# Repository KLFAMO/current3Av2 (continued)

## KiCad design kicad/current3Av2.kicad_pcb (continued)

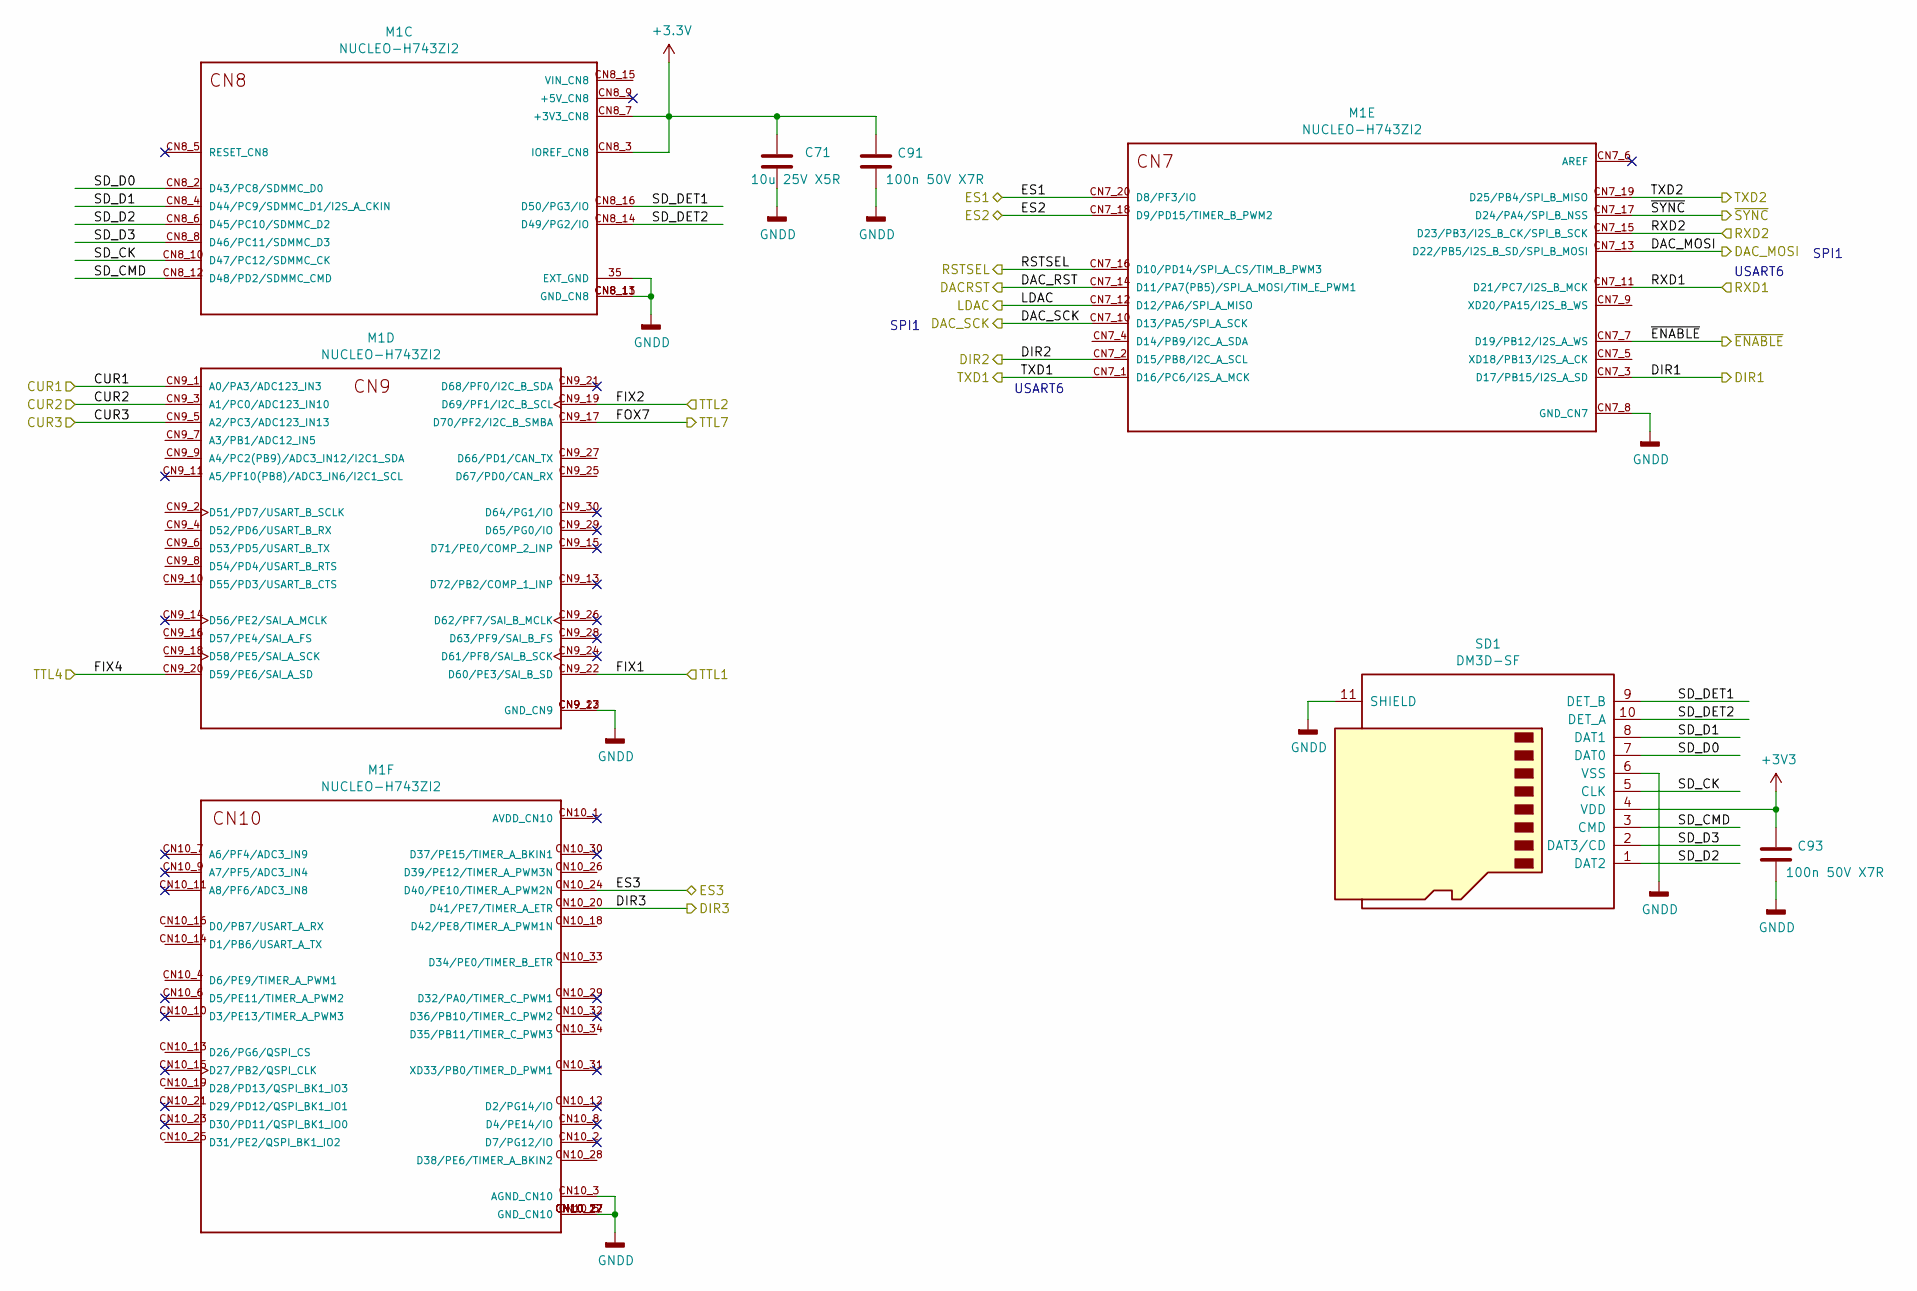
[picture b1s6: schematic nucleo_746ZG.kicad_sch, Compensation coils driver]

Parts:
C71: 10u 25V X5R; C_0603
C91, C93: 100n 50V X7R; C_0603
M1: NUCLEO-H743ZI2; MODULE_NUCLEO-F746ZG_mini_M
SD1: DM3D-SF; Hirose_DM3D-SF

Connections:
/CUR1: M1.CN9_1 (A0/PA3/ADC123_IN3); also elsewhere on the board
/CUR2: M1.CN9_3 (A1/PC0/ADC123_IN10); also elsewhere on the board
/CUR3: M1.CN9_5 (A2/PC3/ADC123_IN13); also elsewhere on the board
/DIR1: M1.CN7_3 (D17/PB15/I2S_A_SD); also elsewhere on the board
/DIR2: M1.CN7_2 (D15/PB8/I2C_A_SCL); also elsewhere on the board
/DIR3: M1.CN10_20 (D41/PE7/TIMER_A_ETR); also elsewhere on the board
/ES1: M1.CN7_20 (D8/PF3/IO); also elsewhere on the board
/ES2: M1.CN7_18 (D9/PD15/TIMER_B_PWM2); also elsewhere on the board
/ES3: M1.CN10_24 (D40/PE10/TIMER_A_PWM2N); also elsewhere on the board
/controller+DAC/DAC_MOSI: M1.CN7_13 (D22/PB5/I2S_B_SD/SPI_B_MOSI); also elsewhere on the board
/controller+DAC/DAC_SCK: M1.CN7_10 (D13/PA5/SPI_A_SCK); also elsewhere on the board
/controller+DAC/FIX1: M1.CN9_22 (D60/PE3/SAI_B_SD); also elsewhere on the board
/controller+DAC/FIX2: M1.CN9_19 (D69/PF1/I2C_B_SCL); also elsewhere on the board
/controller+DAC/FIX4: M1.CN9_20 (D59/PE6/SAI_A_SD); also elsewhere on the board
/controller+DAC/FOX7: M1.CN9_17 (D70/PF2/I2C_B_SMBA); also elsewhere on the board
/controller+DAC/LDAC: M1.CN7_12 (D12/PA6/SPI_A_MISO); also elsewhere on the board
/controller+DAC/RSTSEL: M1.CN7_16 (D10/PD14/SPI_A_CS/TIM_B_PWM3); also elsewhere on the board
/controller+DAC/RXD1: M1.CN7_11 (D21/PC7/I2S_B_MCK); also elsewhere on the board
/controller+DAC/RXD2: M1.CN7_15 (D23/PB3/I2S_B_CK/SPI_B_SCK); also elsewhere on the board
/controller+DAC/TXD1: M1.CN7_1 (D16/PC6/I2S_A_MCK); also elsewhere on the board
/controller+DAC/TXD2: M1.CN7_19 (D25/PB4/SPI_B_MISO); also elsewhere on the board
/controller+DAC/nucleo_746ZG/SD_CK: M1.CN8_10 (D47/PC12/SDMMC_CK), SD1.5 (CLK)
/controller+DAC/nucleo_746ZG/SD_CMD: M1.CN8_12 (D48/PD2/SDMMC_CMD), SD1.3 (CMD)
/controller+DAC/nucleo_746ZG/SD_D0: M1.CN8_2 (D43/PC8/SDMMC_D0), SD1.7 (DAT0)
/controller+DAC/nucleo_746ZG/SD_D1: M1.CN8_4 (D44/PC9/SDMMC_D1/I2S_A_CKIN), SD1.8 (DAT1)
/controller+DAC/nucleo_746ZG/SD_D2: M1.CN8_6 (D45/PC10/SDMMC_D2), SD1.1 (DAT2)
/controller+DAC/nucleo_746ZG/SD_D3: M1.CN8_8 (D46/PC11/SDMMC_D3), SD1.2 (DAT3/CD)
/controller+DAC/nucleo_746ZG/SD_DET1: M1.CN8_16 (D50/PG3/IO), SD1.9 (DET_B)
/controller+DAC/nucleo_746ZG/SD_DET2: M1.CN8_14 (D49/PG2/IO), SD1.10 (DET_A)
/controller+DAC/~ENABLE: M1.CN7_7 (D19/PB12/I2S_A_WS); also elsewhere on the board
/controller+DAC/~SYNC: M1.CN7_17 (D24/PA4/SPI_B_NSS); also elsewhere on the board
GND: C71.2, C91.2, C93.2, M1.35 (EXT_GND), M1.CN7_8 (GND_CN7), M1.CN8_11 (GND_CN8), M1.CN8_13 (GND_CN8), M1.CN9_12 (GND_CN9), M1.CN9_23 (GND_CN9), M1.CN10_3 (AGND_CN10), M1.CN10_5 (GND_CN10), M1.CN10_17 (GND_CN10), M1.CN10_22 (GND_CN10), M1.CN10_27 (GND_CN10), SD1.6 (VSS), SD1.11 (SHIELD); also elsewhere on the board

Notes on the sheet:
SPI1
USART6

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
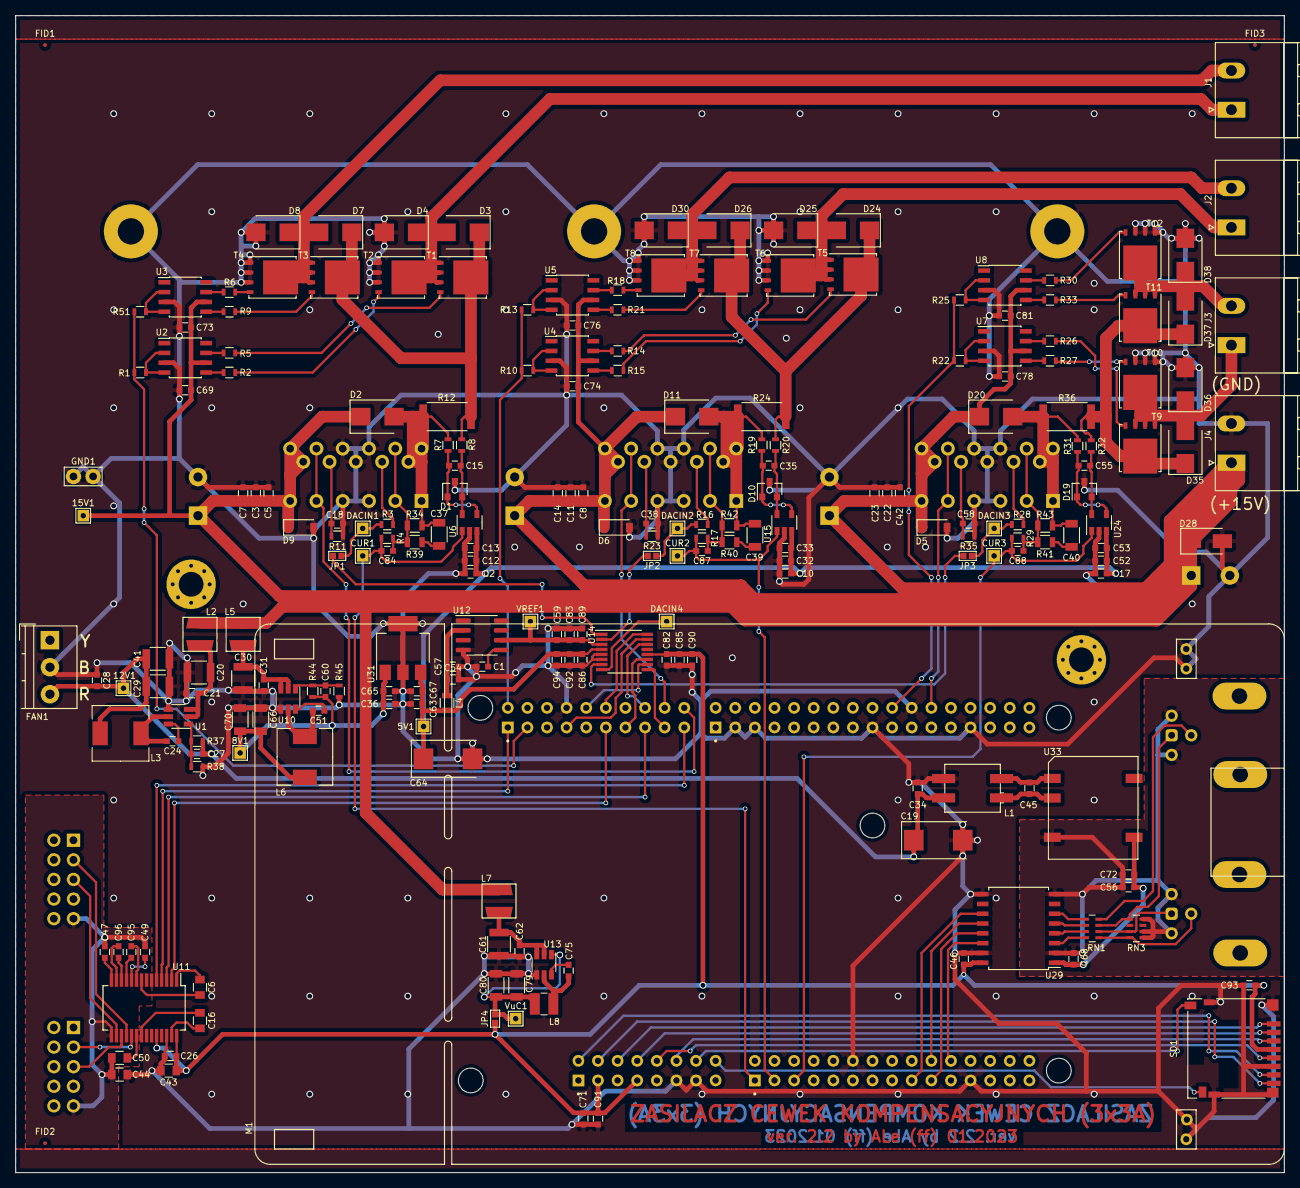
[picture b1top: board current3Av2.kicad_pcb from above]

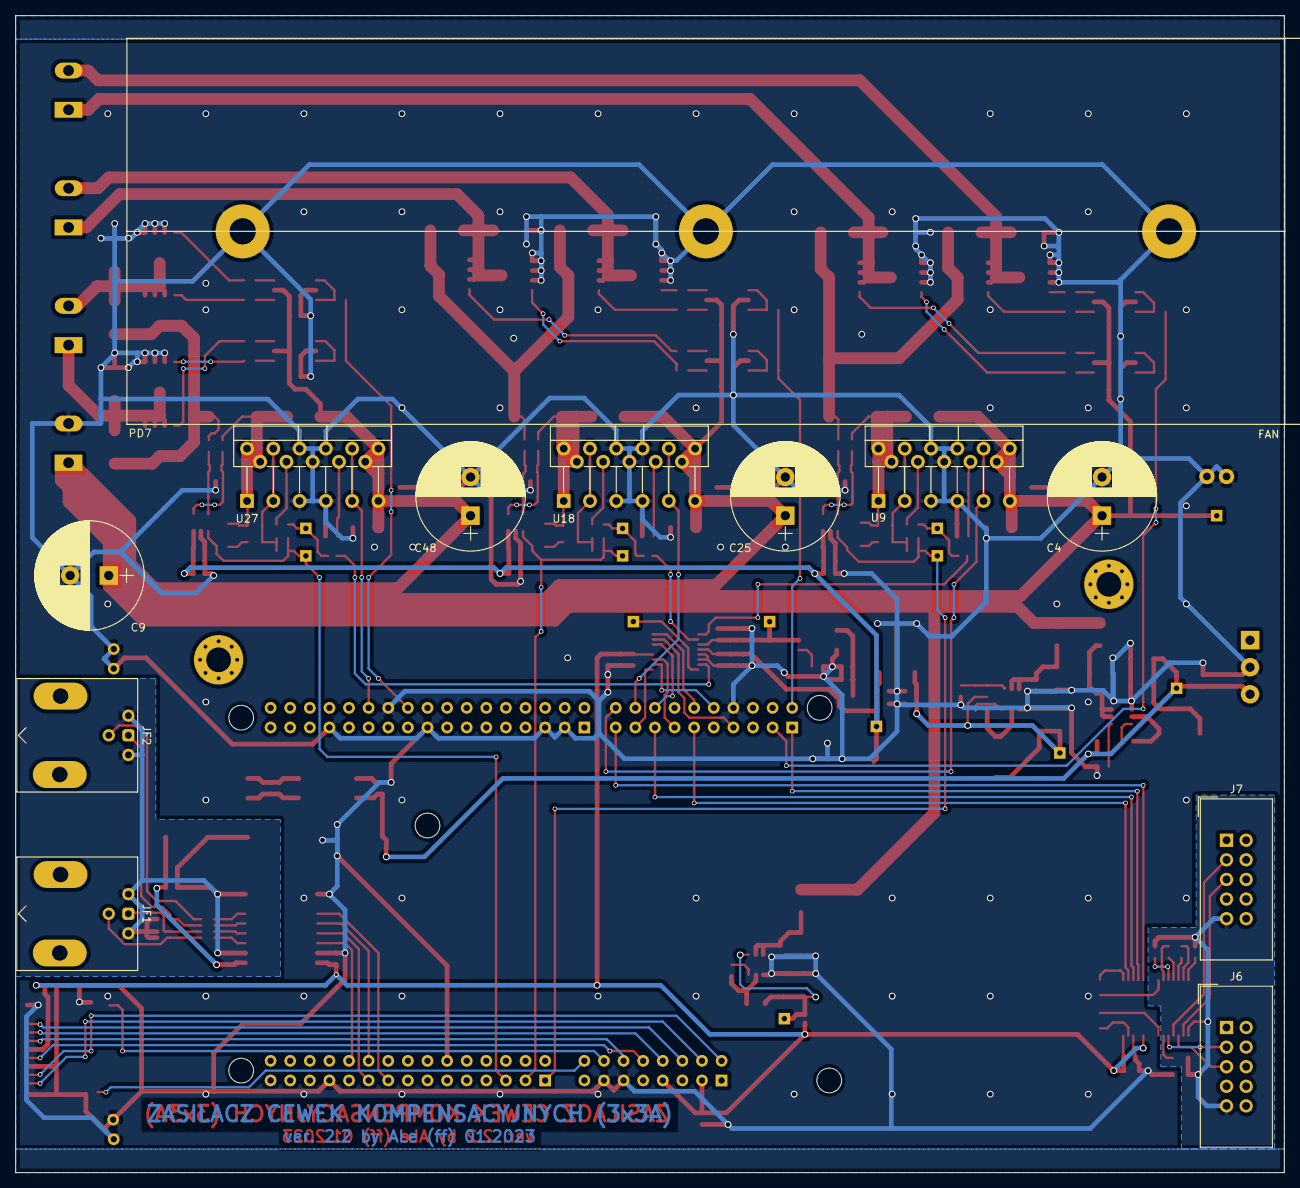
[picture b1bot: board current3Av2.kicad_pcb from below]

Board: 2 copper layers, 164.3 x 149.9 mm, 241 parts (12 on the bottom side), 147 nets.

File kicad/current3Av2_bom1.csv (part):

"Source:","D:\Projekty\FAMO\current3Av2\current3Av2.sch"
"Date:","03.01.2023 12:33:08"
"Tool:","Eeschema (5.1.12)-1"
"Generator:","C:\Program Files\KiCad\bin\scripting\plugins/bom_csv_grouped_by_value.py"
"Component Count:","241"

"Individual Components:"

"Item","Qty","Reference(s)","Value","LibPart","Footprint","Datasheet","Comm","Vendor"
"","","5V1","TestPoint","Connector:TestPoint","Connectors_TestPoints:Test_Point_THTPad_1.5x1.5mm_Drill0.7mm","~","",""
"","","8V1","TestPoint","Connector:TestPoint","Connectors_TestPoints:Test_Point_THTPad_1.5x1.5mm_Drill0.7mm","~","",""
"","","12V1","TestPoint","Connector:TestPoint","Connectors_TestPoints:Test_Point_THTPad_1.5x1.5mm_Drill0.7mm","~","",""
"","","15V1","TestPoint","Connector:TestPoint","Connectors_TestPoints:Test_Point_THTPad_1.5x1.5mm_Drill0.7mm","~","",""
"","","C1","1n C0G 50V","Device:C","Capacitors_SMD:C_0603","~","",""
"","","C2","10u 25V X5R","Device:C","Capacitors_SMD:C_0603","~","GRM188R61E106KA73D",""
"","","C3","10u 25V X5R","Device:C","Capacitors_SMD:C_0603","~","GRM188R61E106KA73D",""
"","","C4","2200u 16V 105°C ","Device:CP","Capacitors_THT:CP_Radial_D14.0mm_P5.00mm","~",">5000h Ø13x25mm P=5mm",""
"","","C5","100n 50V X7R","Device:C","Capacitors_SMD:C_0603","~","",""
"","","C6","470n 100V X7R","Device:C","Capacitors_SMD:C_0805","~","",""
"","","C7","10u 25V X5R","Device:C","Capacitors_SMD:C_0603","~","GRM188R61E106KA73D",""
"","","C8","100n 50V X7R","Device:C","Capacitors_SMD:C_0603","~","",""
"","","C9","2200u 16V 105°C ","Device:CP","Capacitors_THT:CP_Radial_D14.0mm_P5.00mm","~",">5000h Ø13x25mm P=5mm",""
"","","C10","10u 25V X5R","Device:C","Capacitors_SMD:C_0603","~","GRM188R61E106KA73D",""
"","","C11","10u 25V X5R","Device:C","Capacitors_SMD:C_0603","~","GRM188R61E106KA73D",""
"","","C12","100n 50V X7R","Device:C","Capacitors_SMD:C_0603","~","",""
"","","C13","100p C0G 50V","Device:C","Capacitors_SMD:C_0603","~","",""
"","","C14","10u 25V X5R","Device:C","Capacitors_SMD:C_0603","~","GRM188R61E106KA73D",""
"","","C15","1n C0G 50V","Device:C","Capacitors_SMD:C_0603","~","",""
"","","C16","470n 100V X7R","Device:C","Capacitors_SMD:C_0805","~","",""
"","","C17","10u 25V X5R","Device:C","Capacitors_SMD:C_0603","~","GRM188R61E106KA73D",""
"","","C18","100n 50V X7R","Device:C","Capacitors_SMD:C_0603","~","",""
"","","C19","100u 16V","Device:CP","Capacitors_Tantalum_SMD:CP_Tantalum_Case-D_EIA-7343-31_Reflow","~","tantal, case D",""
"","","C20","GRM32ER71H106KA12L","Device:C","Capacitors_SMD:C_1210","~","10u 50V X7R Murata",""
"","","C21","100n 50V X7R","Device:C","Capacitors_SMD:C_0603","~","",""
"","","C22","10u 25V X5R","Device:C","Capacitors_SMD:C_0603","~","GRM188R61E106KA73D",""
"","","C23","10u 25V X5R","Device:C","Capacitors_SMD:C_0603","~","GRM188R61E106KA73D",""
"","","C24","100n 50V X7R","Device:C","Capacitors_SMD:C_0603","~","",""
"","","C25","2200u 16V 105°C ","Device:CP","Capacitors_THT:CP_Radial_D14.0mm_P5.00mm","~",">5000h Ø13x25mm P=5mm",""
"","","C26","100n 50V X7R","Device:C","Capacitors_SMD:C_0603","~","",""
"","","C27","56p 50V C0G","Device:C","Capacitors_SMD:C_0603","~","",""
"","","C28","10u 25V X5R","Device:C","Capacitors_SMD:C_0603","~","GRM188R61E106KA73D",""
"","","C29","GRM32ER71E226KE15K","Device:C","Capacitors_SMD:C_1210","~","22u 25V X7R Murata",""
"","","C30","GRM32ER71H106KA12L","Device:C","Capacitors_SMD:C_1210","~","10u 50V X7R Murata",""
"","","C31","100n 50V X7R","Device:C","Capacitors_SMD:C_0603","~","",""
"","","C32","100n 50V X7R","Device:C","Capacitors_SMD:C_0603","~","",""
"","","C33","100p C0G 50V","Device:C","Capacitors_SMD:C_0603","~","",""
"","","C34","10u 25V X5R","Device:C","Capacitors_SMD:C_0603","~","GRM188R61E106KA73D",""
"","","C35","1n C0G 50V","Device:C","Capacitors_SMD:C_0603","~","",""
"","","C36","10u 25V X5R","Device:C","Capacitors_SMD:C_0603","~","GRM188R61E106KA73D",""
"","","C37","100n 50V C0G","Device:C","Capacitors_SMD:C_1206","~","",""
"","","C38","100n 50V X7R","Device:C","Capacitors_SMD:C_0603","~","",""
"","","C39","100n 50V C0G","Device:C","Capacitors_SMD:C_1206","~","",""
"","","C40","100n 50V C0G","Device:C","Capacitors_SMD:C_1206","~","",""
"","","C41","GRM32ER71E226KE15K","Device:C","Capacitors_SMD:C_1210","~","22u 25V X7R Murata",""
"","","C42","100n 50V X7R","Device:C","Capacitors_SMD:C_0603","~","",""
"","","C43","2,2u 25V X7R","Device:C","Capacitors_SMD:C_0805","~","",""
"","","C44","10n 100V X7R","Device:C","Capacitors_SMD:C_0805","~","",""
"","","C45","10u 25V X5R","Device:C","Capacitors_SMD:C_0603","~","GRM188R61E106KA73D",""
"","","C46","100n 50V X7R","Device:C","Capacitors_SMD:C_0603","~","",""
"","","C47","470n 25V X7R","Device:C","Capacitors_SMD:C_0603","~","",""
"","","C48","2200u 16V 105°C ","Device:CP","Capacitors_THT:CP_Radial_D14.0mm_P5.00mm","~",">5000h Ø13x25mm P=5mm",""
"","","C49","470n 25V X7R","Device:C","Capacitors_SMD:C_0603","~","",""
"","","C50","2,2u 25V X7R","Device:C","Capacitors_SMD:C_0805","~","",""
"","","C51","100n 50V X7R","Device:C","Capacitors_SMD:C_0603","~","",""
"","","C52","100n 50V X7R","Device:C","Capacitors_SMD:C_0603","~","",""
"","","C53","100p C0G 50V","Device:C","Capacitors_SMD:C_0603","~","",""
"","","C54","10u 25V X5R","Device:C","Capacitors_SMD:C_0603","~","GRM188R61E106KA73D",""
"","","C55","1n C0G 50V","Device:C","Capacitors_SMD:C_0603","~","",""
"","","C56","10u 25V X5R","Device:C","Capacitors_SMD:C_0603","~","GRM188R61E106KA73D",""
"","","C57","1u 25V X7R","Device:C","Capacitors_SMD:C_0603","~","",""
"","","C58","100n 50V X7R","Device:C","Capacitors_SMD:C_0603","~","",""
"","","C59","1u 25V X7R","Device:C","Capacitors_SMD:C_0603","~","",""
"","","C60","82p 50V C0G","Device:C","Capacitors_SMD:C_0603","~","",""
"","","C61","GRM32ER71H106KA12L","Device:C","Capacitors_SMD:C_1210","~","10u 50V X7R Murata",""
"","","C62","100n 50V X7R","Device:C","Capacitors_SMD:C_0603","~","",""
"","","C63","10u 25V X5R","Device:C","Capacitors_SMD:C_0603","~","GRM188R61E106KA73D",""
"","","C64","100u 16V","Device:CP","Capacitors_Tantalum_SMD:CP_Tantalum_Case-D_EIA-7343-31_Reflow","~","tantal, case D",""
"","","C65","100n 50V X7R","Device:C","Capacitors_SMD:C_0603","~","",""
"","","C66","GRM31CR71A226KE15L","Device:C","Capacitors_SMD:C_1206","~","22u 10V X7R Murata",""
"","","C67","100n 50V X7R","Device:C","Capacitors_SMD:C_0603","~","",""
"","","C68","100n 50V X7R","Device:C","Capacitors_SMD:C_0603","~","",""
"","","C69","100n 50V X7R","Device:C","Capacitors_SMD:C_0603","~","",""
"","","C70","GRM31CR71A226KE15L","Device:C","Capacitors_SMD:C_1206","~","22u 10V X7R Murata",""
"","","C71","10u 25V X5R","Device:C","Capacitors_SMD:C_0603","~","GRM188R61E106KA73D",""
"","","C72","100n 50V X7R","Device:C","Capacitors_SMD:C_0603","~","",""
"","","C73","100p C0G 50V","Device:C","Capacitors_SMD:C_0603","~","",""
"","","C74","100n 50V X7R","Device:C","Capacitors_SMD:C_0603","~","",""
"","","C75","100n 50V X7R","Device:C","Capacitors_SMD:C_0603","~","",""
"","","C76","100p C0G 50V","Device:C","Capacitors_SMD:C_0603","~","",""
"","","C78","100n 50V X7R","Device:C","Capacitors_SMD:C_0603","~","",""
"","","C79","GRM31CR71A226KE15L","Device:C","Capacitors_SMD:C_1206","~","22u 10V X7R Murata",""
"","","C80","GRM31CR71A226KE15L","Device:C","Capacitors_SMD:C_1206","~","22u 10V X7R Murata",""
"","","C81","100p C0G 50V","Device:C","Capacitors_SMD:C_0603","~","",""
"","","C82","100p 50V C0G","Device:C","Capacitors_SMD:C_0603","~","",""
"","","C83","100n 50V X7R","Device:C","Capacitors_SMD:C_0603","~","",""
"","","C84","DNP","Device:C","Capacitors_SMD:C_0603","~","",""
"","","C85","100n 50V X7R","Device:C","Capacitors_SMD:C_0603","~","",""
"","","C86","100p 50V C0G","Device:C","Capacitors_SMD:C_0603","~","",""
"","","C87","DNP","Device:C","Capacitors_SMD:C_0603","~","",""
"","","C88","DNP","Device:C","Capacitors_SMD:C_0603","~","",""
"","","C89","100p 50V C0G","Device:C","Capacitors_SMD:C_0603","~","",""
"","","C90","10u 25V X5R","Device:C","Capacitors_SMD:C_0603","~","GRM188R61E106KA73D",""
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
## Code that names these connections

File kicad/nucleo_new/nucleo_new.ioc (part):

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Mcu.Name=STM32H743ZITx
Mcu.Package=LQFP144
Mcu.UserName=STM32H743ZITx
PA1.Mode=RMII
PA1.Signal=ETH_REF_CLK
PA11.Mode=Device_Only
PA11.Signal=USB_OTG_FS_DM
PA12.Mode=Device_Only
PA12.Signal=USB_OTG_FS_DP
PA2.Mode=RMII
PA2.Signal=ETH_MDIO
PA3.GPIOParameters=GPIO_Label
PA3.GPIO_Label=CUR3
PA3.Signal=ADCx_INP15
PA5.GPIOParameters=GPIO_Label
PA5.GPIO_Label=A20
PA5.Signal=COMP_DAC12_group
PA7.Mode=RMII
PA7.Signal=ETH_CRS_DV
PA8.Mode=Activate_SOF_FS
PA8.Signal=USB_OTG_FS_SOF
PA9.Mode=Activate_VBUS
PA9.Signal=USB_OTG_FS_VBUS
PB0.GPIOParameters=GPIO_Label
PB0.GPIO_Label=LD1 [Green Led]
PB0.Signal=GPIO_Output
PB13.Mode=RMII
PB13.Signal=ETH_TXD1
PB14.GPIOParameters=GPIO_Label
PB14.GPIO_Label=LD3 [Red Led]
PB14.Signal=GPIO_Output
PB8.GPIOParameters=GPIO_Label
PB8.GPIO_Label=DIR3
PB8.Signal=GPIO_Output
PB9.GPIOParameters=GPIO_Label
PB9.GPIO_Label=DIR2
PB9.Signal=GPIO_Output
PC0.GPIOParameters=GPIO_Label
PC0.GPIO_Label=CUR2
PC0.Signal=ADCx_INP10
PC1.Mode=RMII
PC1.Signal=ETH_MDC
PC10.GPIOParameters=GPIO_Label
PC10.GPIO_Label=SD_D2
PC10.Mode=SD_4_bits_Wide_bus
PC10.Signal=SDMMC1_D2
PC11.GPIOParameters=GPIO_Label
PC11.GPIO_Label=SD_D3
PC11.Mode=SD_4_bits_Wide_bus
PC11.Signal=SDMMC1_D3
PC12.GPIOParameters=GPIO_Label
PC12.GPIO_Label=SD_CK
PC12.Mode=SD_4_bits_Wide_bus
PC12.Signal=SDMMC1_CK
PC13.GPIOParameters=GPIO_Label
PC13.GPIO_Label=B1 [Blue PushButton]
PC13.Signal=GPIO_Input
PC14-OSC32_IN\ (OSC32_IN).Mode=LSE-External-Oscillator
PC14-OSC32_IN\ (OSC32_IN).Signal=RCC_OSC32_IN
PC15-OSC32_OUT\ (OSC32_OUT).Mode=LSE-External-Oscillator
PC15-OSC32_OUT\ (OSC32_OUT).Signal=RCC_OSC32_OUT
PC2_C.GPIOParameters=GPIO_Label
PC2_C.GPIO_Label=CUR1
PC2_C.Mode=IN0-Single-Ended
PC2_C.Signal=ADC3_INP0
PC4.Mode=RMII
PC4.Signal=ETH_RXD0
PC5.Mode=RMII
PC5.Signal=ETH_RXD1
PC6.GPIOParameters=GPIO_Label
PC6.GPIO_Label=TXD1
PC6.Mode=Asynchronous
PC6.Signal=USART6_TX
PC7.GPIOParameters=GPIO_Label
PC7.GPIO_Label=RXD1
PC7.Mode=Asynchronous
PC7.Signal=USART6_RX
PC8.GPIOParameters=GPIO_Label
PC8.GPIO_Label=SD_D0
PC8.Mode=SD_4_bits_Wide_bus
PC8.Signal=SDMMC1_D0
PC9.GPIOParameters=GPIO_Label
PC9.GPIO_Label=SD_D1
PC9.Mode=SD_4_bits_Wide_bus
PC9.Signal=SDMMC1_D1
PD0.GPIOParameters=GPIO_Label
PD0.GPIO_Label=FIX2
PD0.Signal=GPIO_Input
PD1.GPIOParameters=GPIO_Label
PD1.GPIO_Label=FIX4
PD1.Signal=GPIO_Input
PD10.GPIOParameters=GPIO_Label
PD10.GPIO_Label=USB_OTG_FS_PWR_EN
PD10.Signal=GPIO_Output
PD2.GPIOParameters=GPIO_Label
PD2.GPIO_Label=SD_CMD
PD2.Mode=SD_4_bits_Wide_bus
PD2.Signal=SDMMC1_CMD
PD3.GPIOParameters=GPIO_Label
PD3.GPIO_Label=FANERR
PD3.Signal=GPIO_Input
PD4.GPIOParameters=GPIO_Label
PD4.GPIO_Label=FANON
PD4.Signal=GPIO_Output
PD5.GPIOParameters=GPIO_Label
PD5.GPIO_Label=TXD2
PD5.Mode=Asynchronous
PD5.Signal=USART2_TX
PD6.GPIOParameters=GPIO_Label
PD6.GPIO_Label=RXD2
PD6.Mode=Asynchronous
PD6.Signal=USART2_RX
PD7.GPIOParameters=GPIO_Label
PD7.GPIO_Label=DIR1
PD7.Signal=GPIO_Output
PD8.GPIOParameters=GPIO_Label
PD8.GPIO_Label=STLINK_RX
PD8.Mode=Asynchronous
PD8.Signal=USART3_TX
PD9.GPIOParameters=GPIO_Label
PD9.GPIO_Label=STLINK_TX
PD9.Mode=Asynchronous
PD9.Signal=USART3_RX
PE1.GPIOParameters=GPIO_Label
PE1.GPIO_Label=LD2 [Yellow Led]
PE1.Signal=GPIO_Output
PE12.GPIOParameters=GPIO_Label
PE12.GPIO_Label=DAC_SCK
PE12.Mode=TX_Only_Simplex_Unidirect_Master
PE12.Signal=SPI4_SCK
PE2.GPIOParameters=GPIO_Label
PE2.GPIO_Label=FIX3
PE2.Signal=GPIO_Input
PE3.GPIOParameters=GPIO_Label
PE3.GPIO_Label=FIX5
PE3.Signal=GPIO_Input
PE4.GPIOParameters=GPIO_Label
PE4.GPIO_Label=DAC_CS1
PE4.Signal=GPIO_Output
PE5.GPIOParameters=GPIO_Label
PE5.GPIO_Label=DAC_CS2
PE5.Signal=GPIO_Output
PE6.GPIOParameters=GPIO_Label
PE6.GPIO_Label=DAC_MOSI
PE6.Mode=TX_Only_Simplex_Unidirect_Master
PE6.Signal=SPI4_MOSI
PE8.GPIOParameters=GPIO_Label
PE8.GPIO_Label=FOX7
PE8.Signal=GPIO_Output
PE9.GPIOParameters=GPIO_Label
PE9.GPIO_Label=FOX8
PE9.Signal=GPIO_Output
PF1.GPIOParameters=GPIO_Label
PF1.GPIO_Label=DAC_CS3
PF1.Signal=GPIO_Output
PF3.GPIOParameters=GPIO_Label
PF3.GPIO_Label=TH1
PF3.Mode=IN5-Single-Ended
PF3.Signal=ADC3_INP5
PF5.GPIOParameters=GPIO_Label
PF5.GPIO_Label=TH2
PF5.Mode=IN4-Single-Ended
PF5.Signal=ADC3_INP4
PG11.Mode=RMII
PG11.Signal=ETH_TX_EN
PG13.Mode=RMII
PG13.Signal=ETH_TXD0
PG2.GPIOParameters=GPIO_Label
PG2.GPIO_Label=SD_DET2
PG2.Signal=GPIO_Input
PG3.GPIOParameters=GPIO_Label
PG3.GPIO_Label=SD_DET1
PG3.Signal=GPIO_Input
PG7.GPIOParameters=GPIO_Label
PG7.GPIO_Label=USB_OTG_FS_OVCR
PG7.Signal=GPXTI7
PH0-OSC_IN\ (PH0).Mode=HSE-External-Clock-Source
PH0-OSC_IN\ (PH0).Signal=RCC_OSC_IN
PH1-OSC_OUT\ (PH1).Signal=RCC_OSC_OUT
RCC.HSE_VALUE=8000000
RCC.SYSCLKFreq_VALUE=64000000
board=NUCLEO-H743ZI2
boardIOC=true

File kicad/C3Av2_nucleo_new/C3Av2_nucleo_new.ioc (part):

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Mcu.Name=STM32H743ZITx
Mcu.Package=LQFP144
Mcu.UserName=STM32H743ZITx
PA1.Mode=RMII
PA1.Signal=ETH_REF_CLK
PA11.Mode=Device_Only
PA11.Signal=USB_OTG_FS_DM
PA12.Mode=Device_Only
PA12.Signal=USB_OTG_FS_DP
PA13\ (JTMS/SWDIO).Mode=JTAG_4_pins
PA13\ (JTMS/SWDIO).Signal=DEBUG_JTMS-SWDIO
PA14\ (JTCK/SWCLK).Mode=JTAG_4_pins
PA14\ (JTCK/SWCLK).Signal=DEBUG_JTCK-SWCLK
PA15\ (JTDI).Mode=JTAG_4_pins
PA15\ (JTDI).Signal=DEBUG_JTDI
PA2.Mode=RMII
PA2.Signal=ETH_MDIO
PA3.GPIOParameters=GPIO_Label
PA3.GPIO_Label=CUR1(ADC1)
PA3.Signal=ADCx_INP15
PA4.GPIOParameters=GPIO_Label
PA4.GPIO_Label=DAC1_CS(out)
PA4.Signal=GPIO_Output
PA5.GPIOParameters=GPIO_Label
PA5.GPIO_Label=DAC_SCK(SPI1)
PA5.Mode=TX_Only_Simplex_Unidirect_Master
PA5.Signal=SPI1_SCK
PA6.GPIOParameters=GPIO_Label
PA6.GPIO_Label=DAC3_CS(out)
PA6.Signal=GPIO_Output
PA7.Mode=RMII
PA7.Signal=ETH_CRS_DV
PA8.Mode=Activate_SOF_FS
PA8.Signal=USB_OTG_FS_SOF
PA9.Mode=Activate_VBUS
PA9.Signal=USB_OTG_FS_VBUS
PB0.GPIOParameters=GPIO_Label
PB0.GPIO_Label=LD1 [Green Led]
PB0.Signal=GPIO_Output
PB11.GPIOParameters=GPIO_Label
PB11.GPIO_Label=FIX2(EXTI11)
PB11.Signal=GPXTI11
PB12.GPIOParameters=GPIO_Label
PB12.GPIO_Label=DAC2_CS(out)
PB12.Signal=GPIO_Output
PB13.Mode=RMII
PB13.Signal=ETH_TXD1
PB14.GPIOParameters=GPIO_Label
PB14.GPIO_Label=LD3 [Red Led]
PB14.Signal=GPIO_Output
PB15.GPIOParameters=GPIO_Label
PB15.GPIO_Label=DIR1(out)
PB15.Signal=GPIO_Output
PB3\ (JTDO/TRACESWO).Mode=JTAG_4_pins
PB3\ (JTDO/TRACESWO).Signal=DEBUG_JTDO-SWO
PB5.GPIOParameters=GPIO_Label
PB5.GPIO_Label=DAC_MOSI(SPI1)
PB5.Mode=TX_Only_Simplex_Unidirect_Master
PB5.Signal=SPI1_MOSI
PB6.GPIOParameters=GPIO_Label
PB6.GPIO_Label=TDX2
PB6.Mode=Asynchronous
PB6.Signal=USART1_TX
PB7.GPIOParameters=GPIO_Label
PB7.GPIO_Label=RXD2
PB7.Mode=Asynchronous
PB7.Signal=USART1_RX
PB8.GPIOParameters=GPIO_Label
PB8.GPIO_Label=DIR2(out)
PB8.Signal=GPIO_Output
PB9.GPIOParameters=GPIO_Label
PB9.GPIO_Label=DIR3(out)
PB9.Signal=GPIO_Output
PC0.GPIOParameters=GPIO_Label
PC0.GPIO_Label=CUR2(ADC2)
PC0.Signal=ADCx_INP10
PC1.Mode=RMII
PC1.Signal=ETH_MDC
PC10.Mode=SD_4_bits_Wide_bus
PC10.Signal=SDMMC1_D2
PC11.Mode=SD_4_bits_Wide_bus
PC11.Signal=SDMMC1_D3
PC12.Mode=SD_4_bits_Wide_bus
PC12.Signal=SDMMC1_CK
PC13.GPIOParameters=GPIO_Label
PC13.GPIO_Label=B1 [Blue PushButton]
PC13.Signal=GPIO_Input
PC14-OSC32_IN\ (OSC32_IN).Mode=LSE-External-Oscillator
PC14-OSC32_IN\ (OSC32_IN).Signal=RCC_OSC32_IN
PC15-OSC32_OUT\ (OSC32_OUT).Mode=LSE-External-Oscillator
PC15-OSC32_OUT\ (OSC32_OUT).Signal=RCC_OSC32_OUT
PC3_C.GPIOParameters=GPIO_Label
PC3_C.GPIO_Label=CUR3(ADC3)
PC3_C.Mode=IN1-Single-Ended
PC3_C.Signal=ADC3_INP1
PC4.Mode=RMII
PC4.Signal=ETH_RXD0
PC5.Mode=RMII
PC5.Signal=ETH_RXD1
PC6.GPIOParameters=GPIO_Label
PC6.GPIO_Label=TXD1
PC6.Mode=Asynchronous
PC6.Signal=USART6_TX
PC7.GPIOParameters=GPIO_Label
PC7.GPIO_Label=RXD1
PC7.Mode=Asynchronous
PC7.Signal=USART6_RX
PC8.Mode=SD_4_bits_Wide_bus
PC8.Signal=SDMMC1_D0
PC9.Mode=SD_4_bits_Wide_bus
PC9.Signal=SDMMC1_D1
PD10.GPIOParameters=GPIO_Label
PD10.GPIO_Label=USB_OTG_FS_PWR_EN
PD10.Signal=GPIO_Output
PD2.Mode=SD_4_bits_Wide_bus
PD2.Signal=SDMMC1_CMD
PD8.GPIOParameters=GPIO_Label
PD8.GPIO_Label=STLINK_RX
PD8.Mode=Asynchronous
PD8.Signal=USART3_TX
PD9.GPIOParameters=GPIO_Label
PD9.GPIO_Label=STLINK_TX
PD9.Mode=Asynchronous
PD9.Signal=USART3_RX
PE0.GPIOParameters=GPIO_Label
PE0.GPIO_Label=FIX1(EXTI0)
PE0.Signal=GPXTI0
PE1.GPIOParameters=GPIO_Label
PE1.GPIO_Label=LD2 [Yellow Led]
PE1.Signal=GPIO_Output
PE10.GPIOParameters=GPIO_Label
PE10.GPIO_Label=FIX4(PE10)
PE10.Signal=GPXTI10
PE12.GPIOParameters=GPIO_Label
PE12.GPIO_Label=FIX5(EXTI12)
PE12.Signal=GPXTI12
PE6.GPIOParameters=GPIO_Label
PE6.GPIO_Label=FIX3(EXTI6)
PE6.Signal=GPXTI6
PE7.GPIOParameters=GPIO_Label
PE7.GPIO_Label=FIX6(EXTI7)
PE7.Signal=GPXTI7
PE8.GPIOParameters=GPIO_Label
PE8.GPIO_Label=FOX7(out)
PE8.Signal=GPIO_Output
PE9.GPIOParameters=GPIO_Label
PE9.GPIO_Label=FOX8(out)
PE9.Signal=GPIO_Output
PG11.Mode=RMII
PG11.Signal=ETH_TX_EN
PG13.Mode=RMII
PG13.Signal=ETH_TXD0
PG2.GPIOParameters=GPIO_Label
PG2.GPIO_Label=SD_DET2(EXTI2)
PG2.Signal=GPXTI2
PG3.GPIOParameters=GPIO_Label
PG3.GPIO_Label=SD_DET1(EXTI3)
PG3.Signal=GPXTI3
PH0-OSC_IN\ (PH0).Mode=HSE-External-Clock-Source
PH0-OSC_IN\ (PH0).Signal=RCC_OSC_IN
PH1-OSC_OUT\ (PH1).Signal=RCC_OSC_OUT
RCC.HSE_VALUE=8000000
RCC.SYSCLKFreq_VALUE=64000000
board=NUCLEO-H743ZI2
boardIOC=true

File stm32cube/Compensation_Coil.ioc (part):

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Mcu.Name=STM32H743ZITx
Mcu.Package=LQFP144
Mcu.UserName=STM32H743ZITx
PA1.GPIOParameters=GPIO_Speed
PA1.GPIO_Speed=GPIO_SPEED_FREQ_HIGH
PA1.Mode=RMII
PA1.Signal=ETH_REF_CLK
PA2.GPIOParameters=GPIO_Speed
PA2.GPIO_Speed=GPIO_SPEED_FREQ_HIGH
PA2.Mode=RMII
PA2.Signal=ETH_MDIO
PA4.GPIOParameters=GPIO_Label
PA4.GPIO_Label=SYNC
PA4.Mode=NSS_Signal_Hard_Output
PA4.Signal=SPI1_NSS
PA5.GPIOParameters=GPIO_Label
PA5.GPIO_Label=DAC_SCK
PA5.Mode=TX_Only_Simplex_Unidirect_Master
PA5.Signal=SPI1_SCK
PA6.GPIOParameters=GPIO_Label
PA6.GPIO_Label=LDAC
PA6.Signal=GPIO_Output
PA7.GPIOParameters=GPIO_Speed
PA7.GPIO_Speed=GPIO_SPEED_FREQ_HIGH
PA7.Mode=RMII
PA7.Signal=ETH_CRS_DV
PB0.GPIOParameters=GPIO_Speed,GPIO_Label
PB0.GPIO_Label=LD1 [Green Led]
PB0.GPIO_Speed=GPIO_SPEED_FREQ_VERY_HIGH
PB0.Signal=GPIO_Output
PB12.GPIOParameters=GPIO_Label
PB12.GPIO_Label=ENABLE
PB12.Signal=GPIO_Output
PB13.GPIOParameters=GPIO_Speed
PB13.GPIO_Speed=GPIO_SPEED_FREQ_HIGH
PB13.Mode=RMII
PB13.Signal=ETH_TXD1
PB14.GPIOParameters=GPIO_Speed,GPIO_Label
PB14.GPIO_Label=LD3 [Red Led]
PB14.GPIO_Speed=GPIO_SPEED_FREQ_VERY_HIGH
PB14.Signal=GPIO_Output
PB15.GPIOParameters=GPIO_Label
PB15.GPIO_Label=DIR1
PB15.Signal=GPIO_Output
PB5.GPIOParameters=GPIO_Label
PB5.GPIO_Label=DAC_MOSI
PB5.Mode=TX_Only_Simplex_Unidirect_Master
PB5.Signal=SPI1_MOSI
PB8.GPIOParameters=GPIO_Label
PB8.GPIO_Label=DIR2
PB8.Signal=GPIO_Output
PC1.GPIOParameters=GPIO_Speed
PC1.GPIO_Speed=GPIO_SPEED_FREQ_HIGH
PC1.Mode=RMII
PC1.Signal=ETH_MDC
PC13.Signal=GPXTI13
PC4.GPIOParameters=GPIO_Speed
PC4.GPIO_Speed=GPIO_SPEED_FREQ_HIGH
PC4.Mode=RMII
PC4.Signal=ETH_RXD0
PC5.GPIOParameters=GPIO_Speed
PC5.GPIO_Speed=GPIO_SPEED_FREQ_HIGH
PC5.Mode=RMII
PC5.Signal=ETH_RXD1
PD14.GPIOParameters=GPIO_Label
PD14.GPIO_Label=RSTSEL
PD14.Signal=GPIO_Output
PD8.GPIOParameters=GPIO_Speed,GPIO_Label
PD8.GPIO_Label=STLINK_RX
PD8.GPIO_Speed=GPIO_SPEED_FREQ_HIGH
PD8.Mode=Asynchronous
PD8.Signal=USART3_TX
PD9.GPIOParameters=GPIO_Speed,GPIO_Label
PD9.GPIO_Label=STLINK_TX
PD9.GPIO_Speed=GPIO_SPEED_FREQ_HIGH
PD9.Mode=Asynchronous
PD9.Signal=USART3_RX
PE1.GPIOParameters=GPIO_Speed,GPIO_Label
PE1.GPIO_Label=LD2 [Yellow Led]
PE1.GPIO_Speed=GPIO_SPEED_FREQ_VERY_HIGH
PE1.Signal=GPIO_Output
PE3.GPIOParameters=GPIO_PuPd,GPIO_Label
PE3.GPIO_Label=TTL1
PE3.GPIO_PuPd=GPIO_PULLDOWN
PE3.Signal=GPIO_Input
PE6.GPIOParameters=GPIO_Label,GPIO_ModeDefaultEXTI
PE6.GPIO_Label=TTL3
PE6.GPIO_ModeDefaultEXTI=GPIO_MODE_IT_RISING
PE6.Signal=GPXTI6
PE7.GPIOParameters=GPIO_Label
PE7.GPIO_Label=DIR3
PE7.Signal=GPIO_Output
PF1.GPIOParameters=GPIO_PuPd,GPIO_Label
PF1.GPIO_Label=TTL2
PF1.GPIO_PuPd=GPIO_PULLDOWN
PF1.Signal=GPIO_Input
PG11.GPIOParameters=GPIO_Speed
PG11.GPIO_Speed=GPIO_SPEED_FREQ_HIGH
PG11.Mode=RMII
PG11.Signal=ETH_TX_EN
PG13.GPIOParameters=GPIO_Speed
PG13.GPIO_Speed=GPIO_SPEED_FREQ_HIGH
PG13.Mode=RMII
PG13.Signal=ETH_TXD0
PH0-OSC_IN\ (PH0).Mode=HSE-External-Clock-Source
PH0-OSC_IN\ (PH0).Signal=RCC_OSC_IN
RCC.HSE_VALUE=8000000
RCC.SYSCLKFreq_VALUE=75000000
RCC.SYSCLKSource=RCC_SYSCLKSOURCE_PLLCLK
board=NUCLEO-H743ZI2
boardIOC=true

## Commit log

2024-01-12 adding kicad project
2024-01-12 Copying Mehrdad Zarei's STM32cubeIDE project from svn KLFAMO repository
2024-01-12 adding Debug/ to .gitignore
2024-01-12 Removing Debug from repository
2024-01-12 adding .settings and *.launch to .gitignore
2024-01-12 adding changelog.md and version.h
2024-01-16 server IP changed to 192.168.3.111
2024-01-16 ADC CUR 1,2,3 config in ioc
2024-01-24 running Mehrdad's program on nem cubeide, remove server ip, commented some code
2024-01-24 commented content of TTL EXTI
2024-01-25 commented content of SPI_TxCpltCallback
2024-01-25 commenting some code
2024-01-25 removed TTLs and DIRs signals from ioc of v1
2024-01-25 removed spi4 from v1
2024-01-25 removed cs1, cs2, cs3 from v1
2024-01-26 static ip 192.168.3.111
2024-02-20 setting some voltage on dac
2024-02-24 SetDAC works
2024-03-05 adding DIR1,2,3 signals to ioc
2024-03-05 adding TTL1,2,3 to ioc
2024-03-05 GPIO_EXTI_Callback partially uncommented and modified to check only 2 TTLs state
2024-03-27 adding kicad backups to gitignore
2024-03-27 changes in SendToDAC up to line 673, not tested yet
2024-03-28 changes in SendToDAC up to line 673, compilation works, not tested yet
2024-03-28 changes in SendToDAC, compilation works, hardware not tested yet
2024-03-28 testing current switching, not working yet
2024-04-02 ramp test, dir3 does not work
2024-04-02 bugfix dir3 works
2024-04-03 clock switched to high speed internal
2024-04-03 minor changes
2024-04-03 version, changelog
2024-04-03 code cleaning
2026-04-28 new cube ide project copy from 100A
2026-04-28 removing 100A code and running - interface works
